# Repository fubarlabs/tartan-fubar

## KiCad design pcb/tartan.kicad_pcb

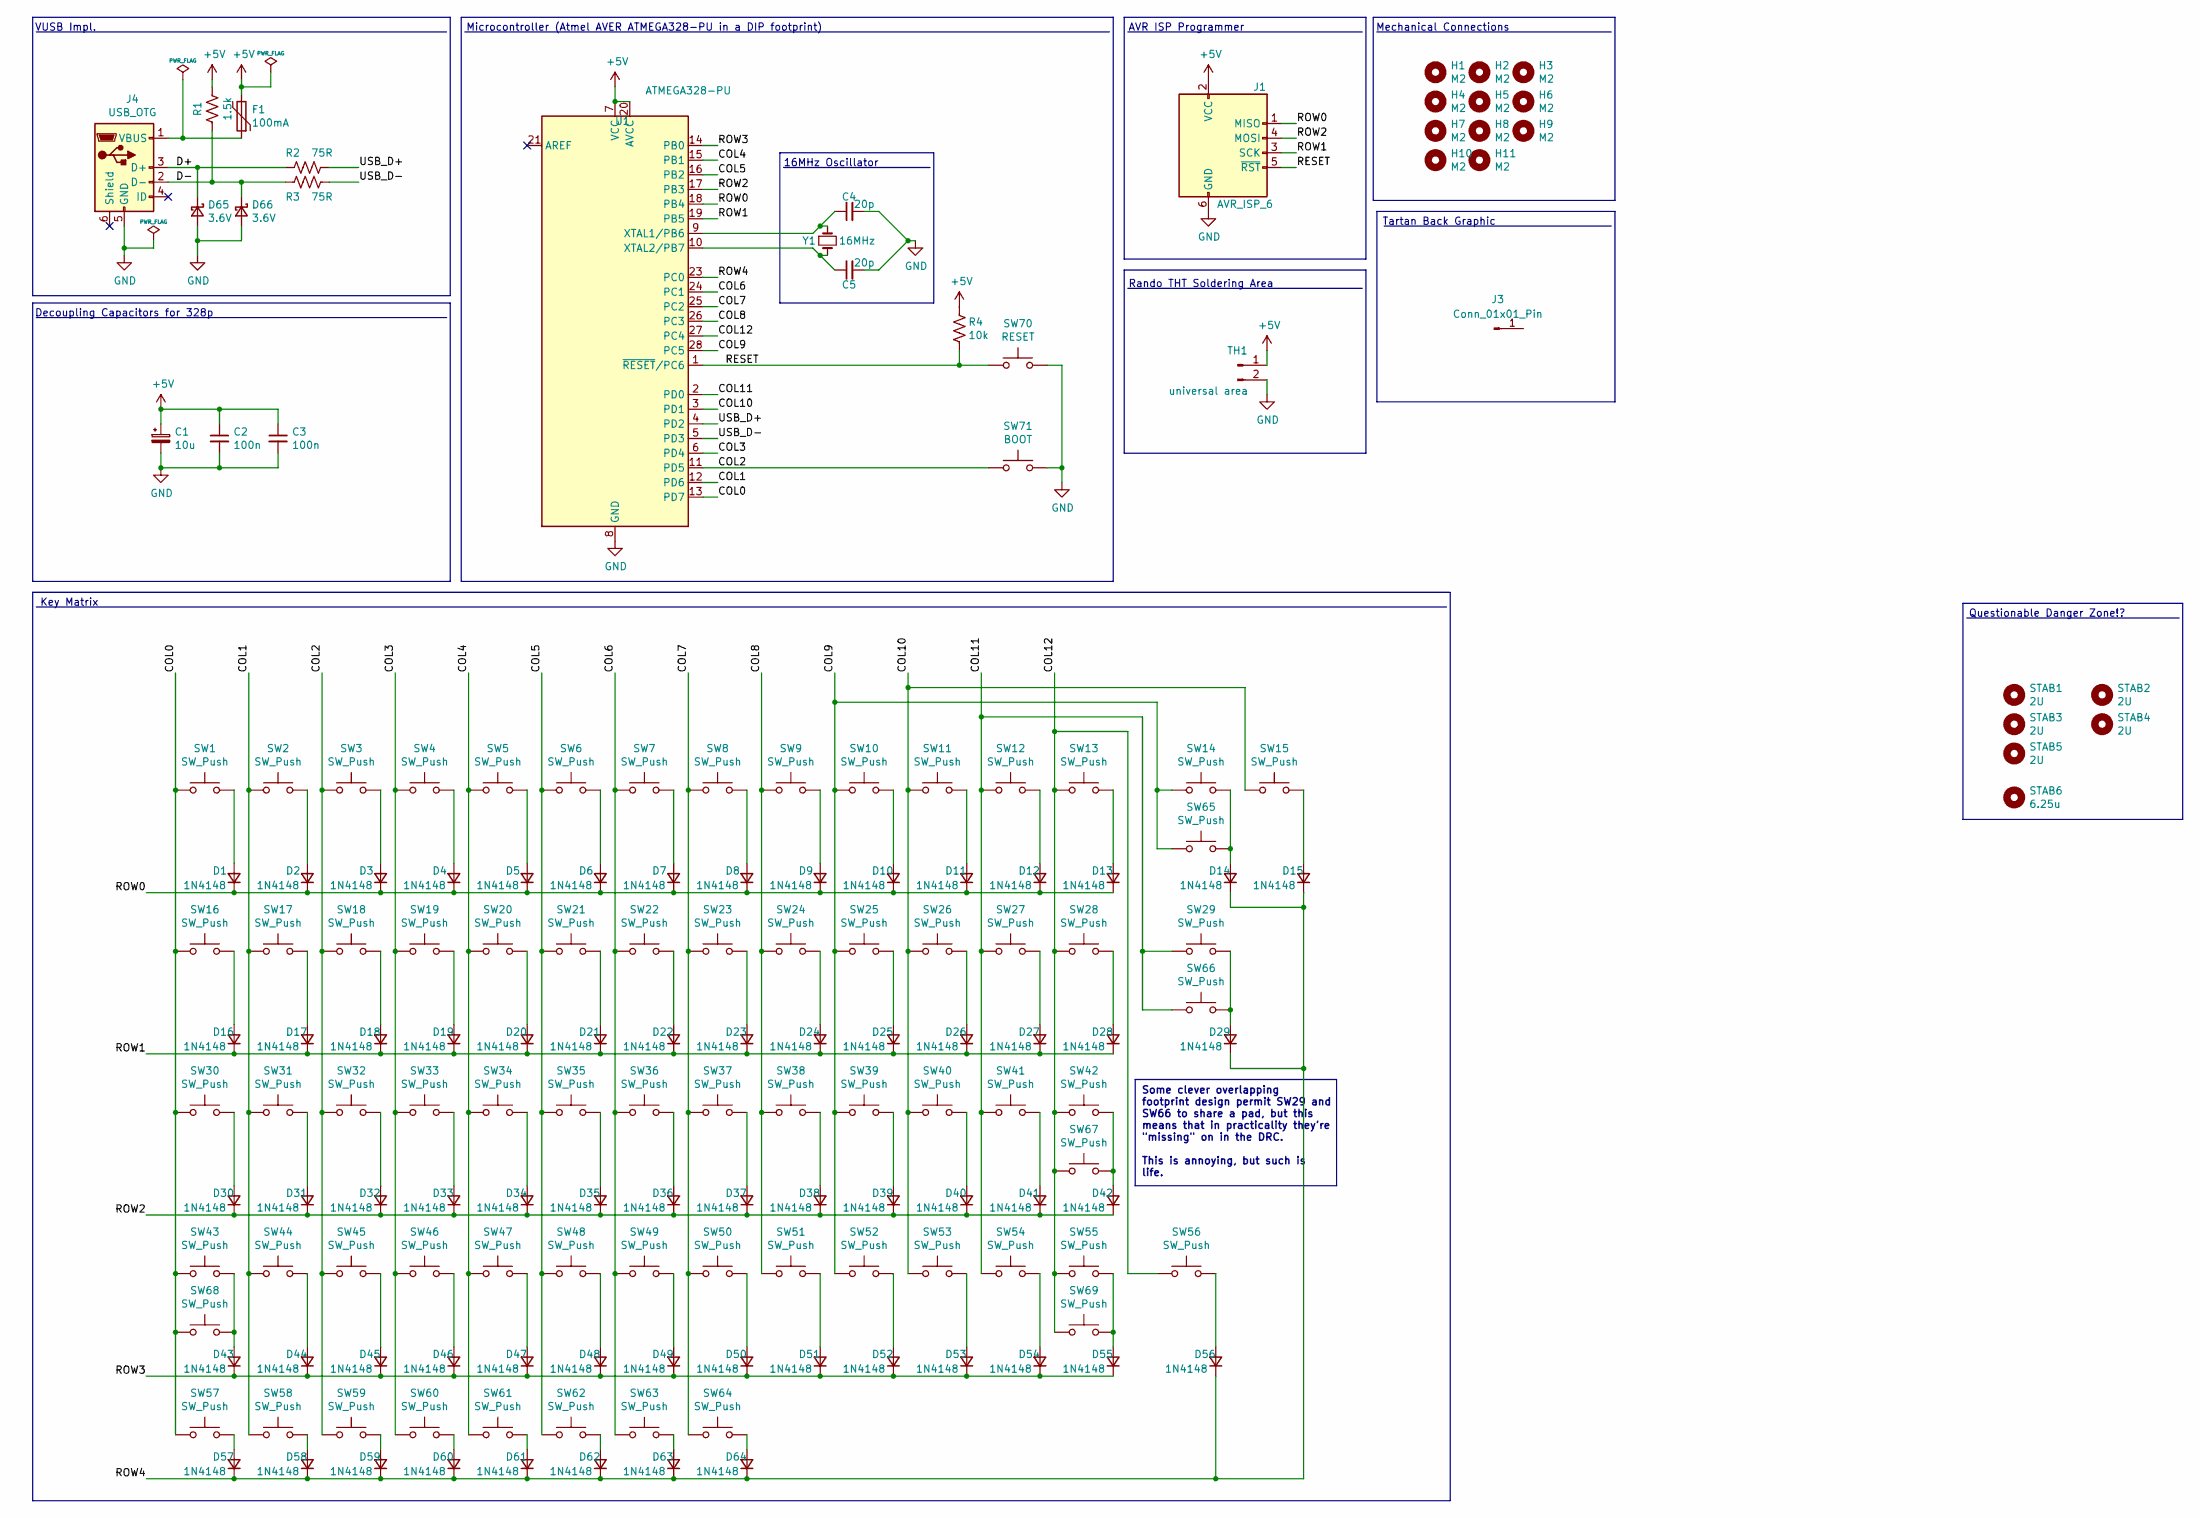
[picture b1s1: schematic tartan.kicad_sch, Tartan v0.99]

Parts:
C1: 10u; CP_Radial_D4.0mm_P1.50mm
C2, C3: 100n; C_Disc_D4.3mm_W1.9mm_P5.00mm
C4, C5: 20p; C_Disc_D3.0mm_W1.6mm_P2.50mm
D1, D2, D3, D4, D5, D6, D7, D8, D9, D10, D11, D12, D13, D14, D15, D16, D17, D18, D19, D20, D21, D22, D23, D24, D25, D26, D27, D28, D29, D30, D31, D32, D33, D34, D35, D36, D37, D38, D39, D40, D41, D42, D43, D44, D45, D46, D47, D48, D49, D50, D51, D52, D53, D54, D55, D56, D57, D58, D59, D60, D61, D62, D63, D64: 1N4148; D_DO-35_SOD27_P5.08mm_Horizontal
D65, D66: 3.6V; D_DO-35_SOD27_P5.08mm_Horizontal
F1: 100mA; polyfuse_5.1mm
H1, H2, H3, H4, H5, H6, H7, H8, H9, H10, H11: M2; MountingHole_2.2mm_M2
J1: AVR_ISP_6; PinHeader_2x03_P2.54mm_Vertical
J3: Conn_01x01_Pin; bottom1_mask
J4: USB_OTG; USB B THT 1734510-1_TEC
R1: 1.5k; R_Axial_DIN0204_L3.6mm_D1.6mm_P5.08mm_Horizontal
R2, R3: 75R; R_Axial_DIN0204_L3.6mm_D1.6mm_P5.08mm_Horizontal
R4: 10k; R_Axial_DIN0204_L3.6mm_D1.6mm_P5.08mm_Horizontal
STAB1, STAB2, STAB3, STAB4, STAB5: 2U; STAB_MX_2u
STAB6: 6.25u; STAB_MX_6.25u
SW1, SW2, SW3, SW4, SW5, SW6, SW7, SW8, SW9, SW10, SW11, SW12, SW13, SW14, SW15, SW17, SW18, SW19, SW20, SW21, SW22, SW23, SW24, SW25, SW26, SW27, SW28, SW31, SW32, SW33, SW34, SW35, SW36, SW37, SW38, SW39, SW40, SW41, SW42, SW43, SW44, SW45, SW46, SW47, SW48, SW49, SW50, SW51, SW52, SW53, SW54, SW56, SW60, SW65, SW67, SW68, SW69: SW_Push; SW_Cherry_MX1A_1.00u_PCB
SW16, SW29: SW_Push; SW_Cherry_MX1A_1.50u_PCB
SW30, SW55: SW_Push; SW_Cherry_MX1A_1.75u_PCB
SW57, SW58, SW59, SW61, SW62, SW63, SW64: SW_Push; SW_Cherry_MX1A_1.25u_PCB
SW66: SW_Push; Tartan_SW_Cherry_MX1A_1.50u_PCB
SW70: RESET; SW_PUSH_6mm
SW71: BOOT; SW_PUSH_6mm
TH1: universal area; universal_area
U1: ATMEGA328-PU; DIP-28_W7.62mm
Y1: 16MHz; Crystal_HC49-4H_Vertical

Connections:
+5V: C1.1, C2.1, C3.1, F1.2, J1.2 (VCC), R1.2, R4.1, TH1.1, U1.7 (VCC), U1.20 (AVCC)
/COL0: SW1.2, SW16.2, SW30.2, SW43.2, SW57.2, SW68.2, U1.13 (PD7)
/COL1: SW2.2, SW17.2, SW31.2, SW44.2, SW58.2, U1.12 (PD6)
/COL2: SW3.2, SW18.2, SW32.2, SW45.2, SW59.2, SW71.1, U1.11 (PD5)
/COL3: SW4.2, SW19.2, SW33.2, SW46.2, SW60.2, U1.6 (PD4)
/COL4: SW5.2, SW20.2, SW34.2, SW47.2, SW61.2, U1.15 (PB1)
/COL5: SW6.2, SW21.2, SW35.2, SW48.2, SW62.2, U1.16 (PB2)
/COL6: SW7.2, SW22.2, SW36.2, SW49.2, SW63.2, U1.24 (PC1)
/COL7: SW8.2, SW23.2, SW37.2, SW50.2, SW64.2, U1.25 (PC2)
/COL8: SW9.2, SW24.2, SW38.2, SW51.2, U1.26 (PC3)
/COL9: SW10.2, SW14.2, SW25.2, SW39.2, SW52.2, SW65.2, U1.28 (PC5)
/COL10: SW11.2, SW15.2, SW26.2, SW40.2, SW53.2, U1.3 (PD1)
/COL11: SW12.2, SW27.2, SW29.2, SW41.2, SW54.2, SW66.2, U1.2 (PD0)
/COL12: SW13.2, SW28.2, SW42.2, SW55.2, SW56.2, SW67.2, SW69.2, U1.27 (PC4)
/D+: D65.1 (K), J4.3 (D+), R2.2
/D-: D66.1 (K), J4.2 (D-), R1.1, R3.2
/RESET: J1.5 (~RST), R4.2, SW70.1, U1.1 (~RESET/PC6)
/ROW0: D1.1 (K), D2.1 (K), D3.1 (K), D4.1 (K), D5.1 (K), D6.1 (K), D7.1 (K), D8.1 (K), D9.1 (K), D10.1 (K), D11.1 (K), D12.1 (K), D13.1 (K), J1.1 (MISO), U1.18 (PB4)
/ROW1: D16.1 (K), D17.1 (K), D18.1 (K), D19.1 (K), D20.1 (K), D21.1 (K), D22.1 (K), D23.1 (K), D24.1 (K), D25.1 (K), D26.1 (K), D27.1 (K), D28.1 (K), J1.3 (SCK), U1.19 (PB5)
/ROW2: D30.1 (K), D31.1 (K), D32.1 (K), D33.1 (K), D34.1 (K), D35.1 (K), D36.1 (K), D37.1 (K), D38.1 (K), D39.1 (K), D40.1 (K), D41.1 (K), D42.1 (K), J1.4 (MOSI), U1.17 (PB3)
/ROW3: D43.1 (K), D44.1 (K), D45.1 (K), D46.1 (K), D47.1 (K), D48.1 (K), D49.1 (K), D50.1 (K), D51.1 (K), D52.1 (K), D53.1 (K), D54.1 (K), D55.1 (K), U1.14 (PB0)
/ROW4: D14.1 (K), D15.1 (K), D29.1 (K), D56.1 (K), D57.1 (K), D58.1 (K), D59.1 (K), D60.1 (K), D61.1 (K), D62.1 (K), D63.1 (K), D64.1 (K), U1.23 (PC0)
/USB_D+: R2.1, U1.4 (PD2)
/USB_D-: R3.1, U1.5 (PD3)
GND: C1.2, C2.2, C3.2, C4.2, C5.2, D65.2 (A), D66.2 (A), J1.6 (GND), J4.5 (GND), SW70.2, SW71.2, TH1.2, U1.8 (GND), U1.22 (GND)
unnamed: D1.2 (A), SW1.1
unnamed: D2.2 (A), SW2.1
unnamed: D3.2 (A), SW3.1
unnamed: D4.2 (A), SW4.1
unnamed: D5.2 (A), SW5.1
unnamed: D6.2 (A), SW6.1
unnamed: D7.2 (A), SW7.1
unnamed: D8.2 (A), SW8.1
unnamed: D9.2 (A), SW9.1
unnamed: D10.2 (A), SW10.1
unnamed: D11.2 (A), SW11.1
unnamed: D12.2 (A), SW12.1
unnamed: D13.2 (A), SW13.1
unnamed: D14.2 (A), SW14.1, SW65.1
unnamed: D15.2 (A), SW15.1
unnamed: D16.2 (A), SW16.1
unnamed: D17.2 (A), SW17.1
unnamed: D18.2 (A), SW18.1
unnamed: D19.2 (A), SW19.1
unnamed: D20.2 (A), SW20.1
unnamed: D21.2 (A), SW21.1
unnamed: D22.2 (A), SW22.1
unnamed: D23.2 (A), SW23.1
unnamed: D24.2 (A), SW24.1
unnamed: D25.2 (A), SW25.1
unnamed: D26.2 (A), SW26.1
unnamed: D27.2 (A), SW27.1
unnamed: D28.2 (A), SW28.1
unnamed: D29.2 (A), SW29.1, SW66.1
unnamed: D30.2 (A), SW30.1
unnamed: D31.2 (A), SW31.1
unnamed: D32.2 (A), SW32.1
unnamed: D33.2 (A), SW33.1
unnamed: D34.2 (A), SW34.1
unnamed: D35.2 (A), SW35.1
unnamed: D36.2 (A), SW36.1
unnamed: D37.2 (A), SW37.1
unnamed: D38.2 (A), SW38.1
unnamed: D39.2 (A), SW39.1
unnamed: D40.2 (A), SW40.1
unnamed: D41.2 (A), SW41.1
unnamed: D42.2 (A), SW42.1, SW67.1
unnamed: D43.2 (A), SW43.1, SW68.1
unnamed: D44.2 (A), SW44.1
unnamed: D45.2 (A), SW45.1
unnamed: D46.2 (A), SW46.1
unnamed: D47.2 (A), SW47.1
unnamed: D48.2 (A), SW48.1
unnamed: D49.2 (A), SW49.1
unnamed: D50.2 (A), SW50.1
unnamed: D51.2 (A), SW51.1
unnamed: D52.2 (A), SW52.1
unnamed: D53.2 (A), SW53.1
unnamed: D54.2 (A), SW54.1
unnamed: D55.2 (A), SW55.1, SW69.1
unnamed: D56.2 (A), SW56.1
unnamed: D57.2 (A), SW57.1
unnamed: D58.2 (A), SW58.1
unnamed: D59.2 (A), SW59.1
unnamed: D60.2 (A), SW60.1
unnamed: D61.2 (A), SW61.1
unnamed: D62.2 (A), SW62.1
unnamed: D63.2 (A), SW63.1
unnamed: D64.2 (A), SW64.1
unnamed: F1.1, J4.1 (VBUS)
unnamed: C4.1, U1.9 (XTAL1/PB6), Y1.1
unnamed: C5.1, U1.10 (XTAL2/PB7), Y1.2

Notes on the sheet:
Some clever overlapping footprint design permit SW29 and SW66 to share a pad, but this means that in practicality they're "missing" on in the DRC. This is annoying, but such is life.
Decoupling Capacitors for 328p
VUSB Impl.
Mechanical Connections
Rando THT Soldering Area
Questionable Danger Zone!?
16MHz Oscillator
Tartan Back Graphic
Key Matrix
AVR ISP Programmer
Microcontroller (Atmel AVER ATMEGA328-PU in a DIP footprint)

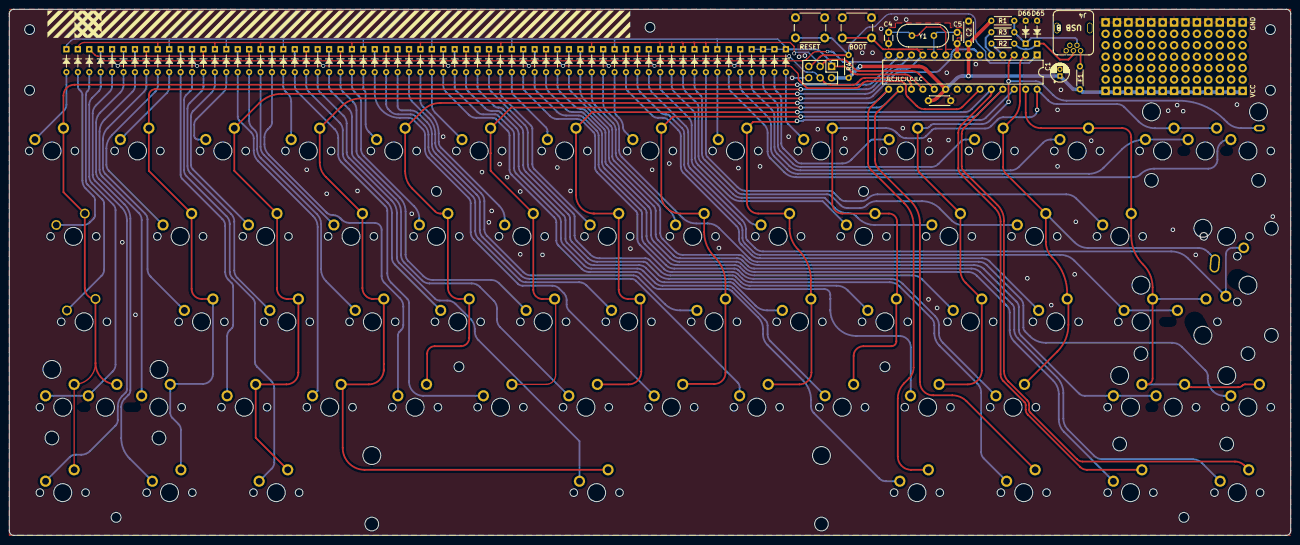
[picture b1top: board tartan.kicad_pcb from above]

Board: 2 copper layers, 285.0 x 117.0 mm, 170 parts (1 on the bottom side), 92 nets.

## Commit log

2023-10-25 Added new routing for matrix, still need to add USB C.
2023-10-26 Fix broken traces and too small vias... hopefully.
2023-11-05 Updated to use new footprints, removed backups directory, as well as specifically removed bottom PCB for sanity savings.
2023-11-05 Little thing called broken traces updated. Rounded some more too I guess.
2023-11-12 Rounded traces and re-added silks. Oops.
2023-11-15 Small cleanup in latest nightly to hopefully minimize truly broken traces.
2023-11-23 Update to new USB B that Ben found.
    new file: pcb/sym-lib-table
2023-12-22 Added stabilizers back and hopefully fixed a bunch of issues (tm).
2024-03-26 Added render pipeline to have screenshots.
2024-03-26 Small typo fix?
2024-03-26 Try again with altered syntax
2024-03-26 Re-indenting "with" tokens.
2024-03-26 indentation for GH pages.
2024-03-26 yet again
2024-03-26 Change to correct file path, ope.
2024-03-26 Fix branch names for old repo type.
2024-03-26 Try outputting to root.
2024-03-26 Change to pwd

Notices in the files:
pcb/tartan.kicad_pcb:
(c)2019 Takuya Urakawa, Dm9Records, 5z6p.com
